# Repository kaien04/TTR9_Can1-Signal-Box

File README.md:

# TTR9_Can1 Signal Box project

Taipei Tech Racing Can1 distribute signal box

## 專案內容
- 相關電路設計圖

## 開發資訊
- 開發者：陳楷恩
- 適用賽事：台灣節能車大賽 / FSAE 相關規格參考

## 目前進度
- [o] 完成基礎電路架構
- [o] 進行 PCB Layout

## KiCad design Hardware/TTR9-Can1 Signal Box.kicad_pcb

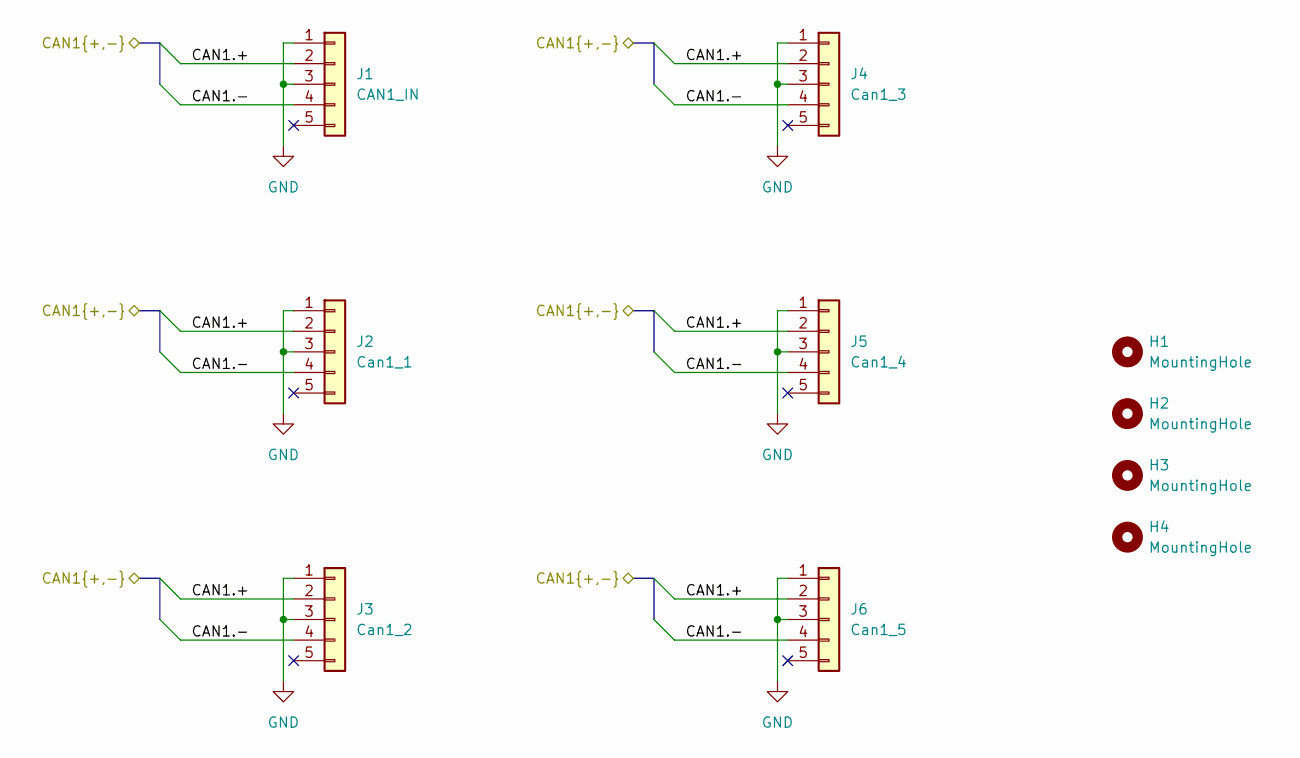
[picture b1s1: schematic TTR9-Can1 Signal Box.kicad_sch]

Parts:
H1, H2, H3, H4: MountingHole; MountingHole_4mm
J1: CAN1_IN; 643260100405
J2: Can1_1; 643260100405
J3: Can1_2; 643260100405
J4: Can1_3; 643260100405
J5: Can1_4; 643260100405
J6: Can1_5; 643260100405

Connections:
/CAN1.+: J1.2, J2.2, J3.2, J4.2, J5.2, J6.2
/CAN1.-: J1.4, J2.4, J3.4, J4.4, J5.4, J6.4
GND: J1.1, J1.3, J2.1, J2.3, J3.1, J3.3, J4.1, J4.3, J5.1, J5.3, J6.1, J6.3

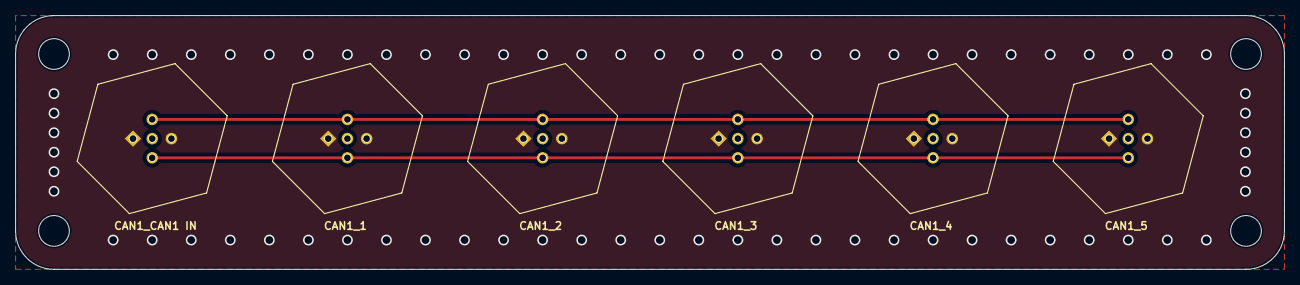
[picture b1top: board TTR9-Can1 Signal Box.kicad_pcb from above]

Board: 2 copper layers, 165.1 x 33.0 mm, 10 parts (0 on the bottom side), 3 nets.

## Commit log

2026-05-11 Initial commit: 新增 Can1 Signal Box 初始電路圖
2026-05-11 del a folder
2026-05-11 Add initial README for TTR9_Can1 Signal Box project
2026-05-12 change Can1 wire wide from 0.2mm to 0.381mm
